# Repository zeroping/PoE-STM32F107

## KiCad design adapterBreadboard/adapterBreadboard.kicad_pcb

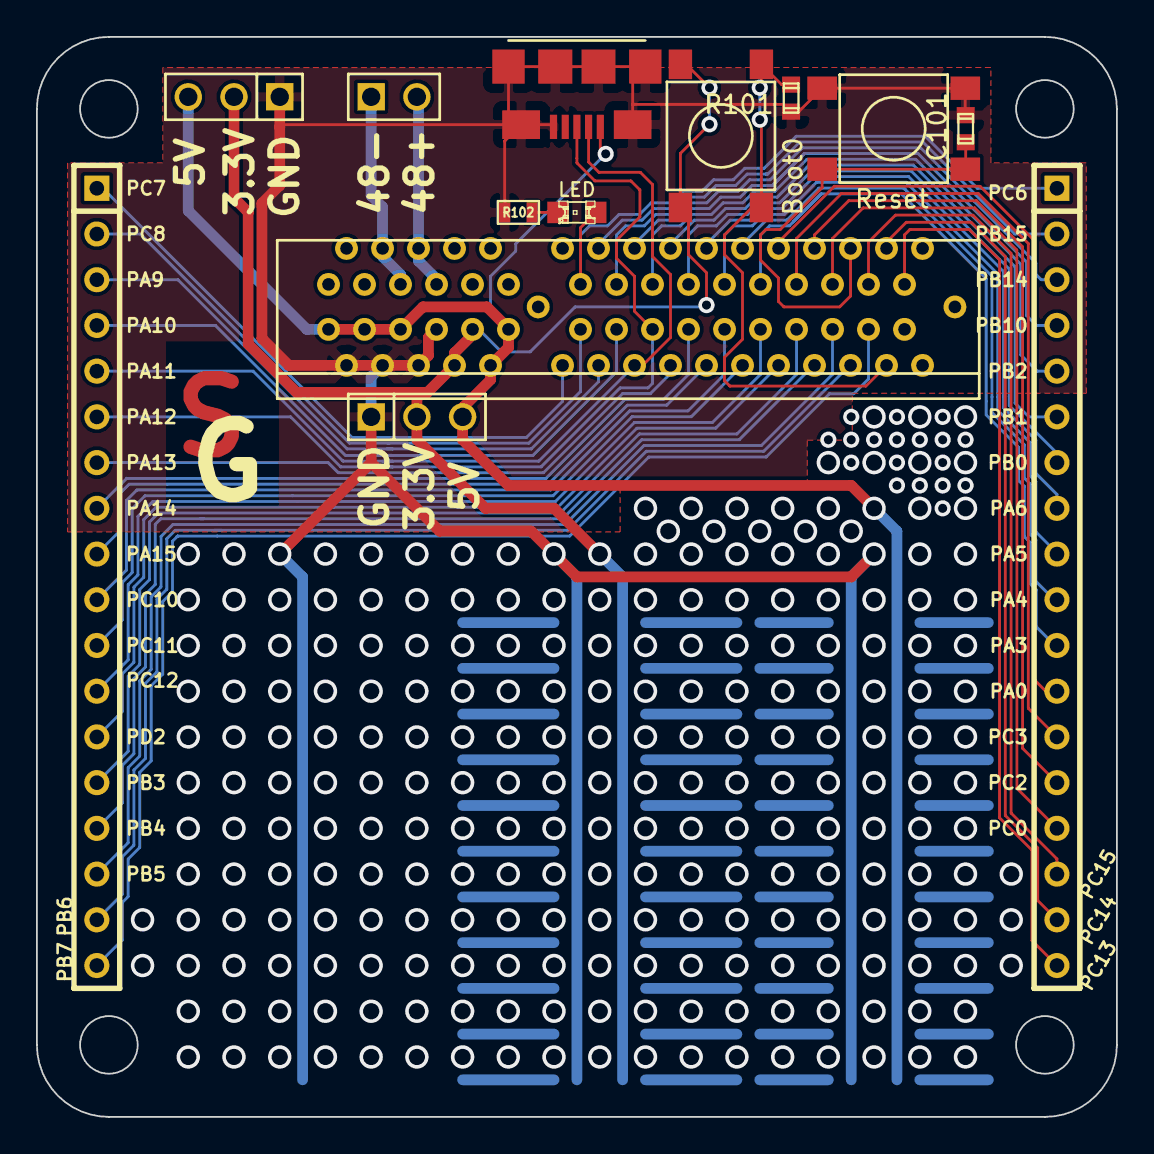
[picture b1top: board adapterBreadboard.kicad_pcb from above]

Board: 2 copper layers, 60.0 x 60.0 mm, 13 parts (0 on the bottom side), 44 nets.

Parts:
C101: 0.1uF; c_0603
D101: LED; LED-0805
J101: USB; mincro-usb
JP101: PCI-E4X_EDGE; con-pci_express(pci-e)-PCI-E_64
K101: PWR; PIN_ARRAY_3X1
K102: CONN_3; PIN_ARRAY_3X1
P101, P102: CONN_19; SIL-18
P103: CONN_2; PIN_ARRAY_2X1
R101: 10K; c_0603
R102: 220; SM0603
SW101: Boot0; tact_sw_4.3mm
SW102: Reset; tact_sw_4.3mm

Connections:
+3.3V: JP101.B8, JP101.B9, K101.2, K102.2, SW101.2
+5V: J101.1, JP101.B1, JP101.B3, JP101.B5, JP101.B10, JP101.B11, K101.3, K102.3
/+48V U +: JP101.A6, JP101.A7, P103.2
/+48V U Return: JP101.A4, JP101.A5, P103.1
/BOOT0: JP101.B30, R101.1, SW101.1
/PA0: JP101.A24, P101.12
/PA3: JP101.A23, P101.11
/PA4: JP101.A22, P101.10
/PA5: JP101.A21, P101.9
/PA6: JP101.A20, P101.8
/PA9: JP101.B14, P102.3
/PA10: JP101.B15, P102.4
/PA11: J101.2, JP101.B16, P102.5
/PA12: J101.3, JP101.B17, P102.6
/PA13: JP101.B18, P102.7
/PA14: JP101.B19, P102.8
/PA15: JP101.B20, P102.9
/PB0: JP101.A19, P101.7
/PB1: JP101.A18, P101.6
/PB2: JP101.A17, P101.5
/PB3: JP101.B25, P102.14
/PB4: JP101.B26, P102.15
/PB5: JP101.B27, P102.16
/PB6: JP101.B28, P102.17
/PB7: JP101.B29, P102.18
/PB10: JP101.A16, P101.4
/PB14: JP101.A15, P101.3
/PB15: JP101.A14, P101.2
/PC0: JP101.A27, P101.15
/PC2: JP101.A26, P101.14
/PC3: JP101.A25, P101.13
/PC6: D101.1, JP101.A13, P101.1
/PC7: JP101.B12, P102.1
/PC8: JP101.B13, P102.2
/PC10: JP101.B21, P102.10
/PC11: JP101.B22, P102.11
/PC12: JP101.B23, P102.12
/PC13: JP101.A31, P101.18
/PC14: JP101.A30, P101.17
/PC15: JP101.A29, P101.16
/PD2: JP101.B24, P102.13
/RESET: C101.1, JP101.A28, SW102.1
GND: C101.2, J101.4, J101.5, J101.6, JP101.B2, JP101.B4, JP101.B6, JP101.B7, K101.1, K102.1, R101.2, R102.2, SW102.2
unnamed: D101.2, R102.1

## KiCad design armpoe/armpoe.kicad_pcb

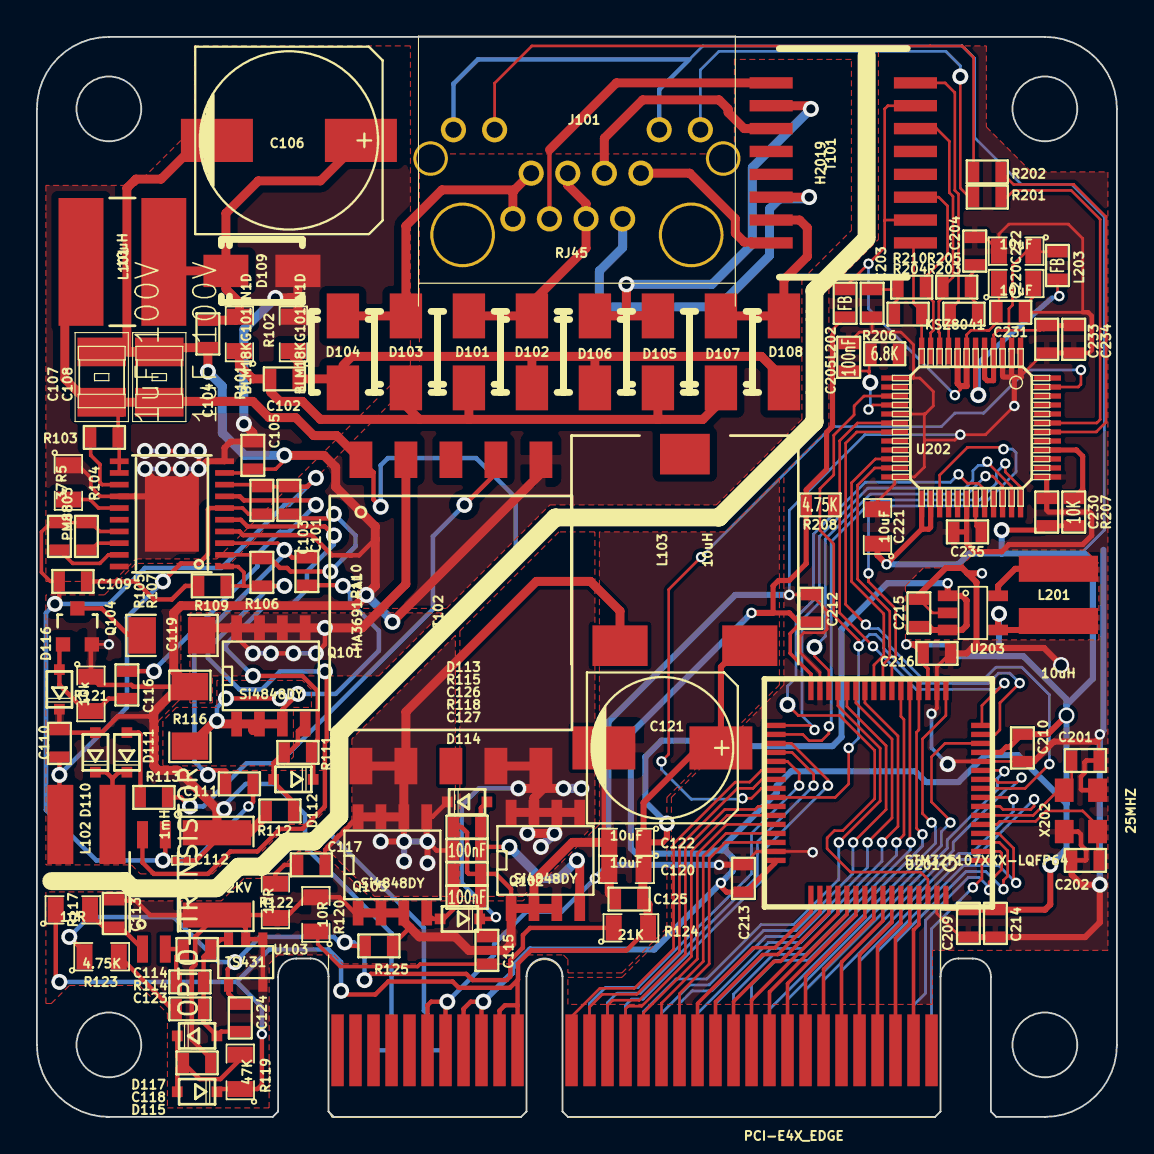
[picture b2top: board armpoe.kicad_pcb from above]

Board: 2 copper layers, 60.0 x 60.0 mm, 119 parts (0 on the bottom side), 119 nets.

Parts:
C101, C103, C110: 1uF 16V; SM0603
C102: 1nF 100V; SM0603
C104, C105: 100nF 100V; SM0603
C106: 33uF 100V; c_elec_10x10.5
C107, C108: 1uF 100V; -C1210
C109, C116, C125, C126, C127, C203, C204, C205, C210, C212, C213, C214, C230, C231, C233, C234, C235: 100nF; SM0603
C111: 470pF; SM0603
C112: 2.2nF 2KV; SM1812
C113, C118: 1uF; SM0603
C114, C123: 22nF; SM0603
C115, C117: 1nF; SM0603
C119: 47nF 200V; SM1206
C120, C122, C220, C221, C222: 10uF; SM0805
C121: 330uF; c_elec_8x10.5
C124: 100pF; SM0603
C201, C202: 18pF; SM0603
C209, C215, C216: 4.7uF; SM0603
D101, D102, D103, D104, D105, D106, D107, D108: STPS1H100A; Diode-SMA_Standard_RevA_26July2010
D109: SMAJ58A; Diode-SMA_Standard_RevA_26July2010
D110, D111, D112, D113, D114, D115, D116, D117: BAT46J; diode-SOD323-mod
J101: RJ45; RJHS-308x
JP201: PCI-E4X_EDGE; con-pci_express(pci-e)-PCI-E_4_EDGE
L101: 10uH; MSS7341
L102: 1mH; LPS4018
L103: 10uH; SER1360
L201: 10uH; LPS4018
L202, L203: FB; SM0603
Q101, Q102, Q103: Si4848DY; Si4848DY-SO8
Q104: Si2325DS; Si2325DS_SOT23
R101, R102: BLM18KG101TN1D; SM0805
R103: 24.9K; SM0603
R104: 37R5; SM0805
R105: 124k; SM0603
R106: 2.7k; SM0603
R107: 60k; SM0603
R108: 0; SM0201_r
R109: 680R; SM0603
R110, R201, R202: 510; SM0603
R111: 22R; SM0603
R112: 100k; SM0603
R113: 10; SM0603
R114: 820R; SM0603
R115, R118: 100K; SM0603
R116: 0.15; SM1206
R117, R120, R122: 10R; SM0805
R119: 47K; SM0805
R121: 10k; SM0805
R123: 4.75K; SM0805
R124: 21K; SM0805
R125, R206: 6.8K; SM0603
R203, R204, R205, R210: 50; SM0603
R207: 10K; SM0603
R208: 4.75K; SM0603
T101: H2019; T1
T102: HA3691-AL; HA3691
U101: PM8803; HTSSOP-20
U102: OPTO-TRANSISTOR; HMHA281
U103: TS431; SOT23-5
U201: STM32F107XXX-LQFP64; LQFP64
U202: KSZ8041; -TQFP48
U203: MCP1603; OS-5
X202: 25MHZ; crystal-ABM8

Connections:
+1.8V: C222.1, C233.1, C234.1, L203.1, U202.4, U202.5
+3.3V: C209.1, C210.1, C212.1, C213.1, C214.1, C216.1, C221.1, C230.1, J101.10, J101.12, JP201.B8, JP201.B9, L201.2, L202.1, R207.1, R208.1, U201.13, U201.19, U201.32, U201.48, U201.64, U202.25, U202.26, U203.4
+5V: C120.1, C121.1, C122.1, C125.1, C215.1, D115.2, JP201.B10, JP201.B11, L103.2, R117.1, R119.1, R124.2, U203.1, U203.3
/48V+ unfiltered input: C104.1, C106.1, D109.2, L101.1, R101.2
/ARTN: C101.2, C103.2, C109.1, C111.2, R105.2, R107.2, R108.2, U101.8, U101.17, U102.4
/CURRENT_SENSE: C111.1, R110.1, U101.3
/DELAY_SET: R107.1, U101.18
/FREQ_SET: R105.1, U101.19
/GAT1: D112.2, R111.1, U101.5
/GAT2: C116.1, U101.7
/MCU/A13: JP201.A13, U201.37
/MCU/A14: JP201.A14, U201.36
/MCU/A15: JP201.A15, U201.35
/MCU/A16: JP201.A16, U201.29
/MCU/A17: JP201.A17, U201.28
/MCU/A18: JP201.A18, U201.27
/MCU/A19: JP201.A19, U201.26
/MCU/A20: JP201.A20, U201.22
/MCU/A21: JP201.A21, U201.21
/MCU/A22: JP201.A22, U201.20
/MCU/A23: JP201.A23, U201.17
/MCU/A24: JP201.A24, U201.14
/MCU/A25: JP201.A25, U201.11
/MCU/A26: JP201.A26, U201.10
/MCU/A27: JP201.A27, U201.8
/MCU/A28: JP201.A28, U201.7
/MCU/A29: JP201.A29, U201.4
/MCU/A30: JP201.A30, U201.3
/MCU/A31: JP201.A31, U201.2
/MCU/A32: JP201.A32, U201.1
/MCU/B12: JP201.B12, U201.38
/MCU/B13: JP201.B13, U201.39
/MCU/B14: JP201.B14, U201.42
/MCU/B15: JP201.B15, U201.43
/MCU/B16: JP201.B16, U201.44
/MCU/B17: JP201.B17, U201.45
/MCU/B18: JP201.B18, U201.46
/MCU/B19: JP201.B19, U201.49
/MCU/B20: JP201.B20, U201.50
/MCU/B21: JP201.B21, U201.51
/MCU/B22: JP201.B22, U201.52
/MCU/B23: JP201.B23, U201.53
/MCU/B24: JP201.B24, U201.54
/MCU/B25: JP201.B25, U201.55
/MCU/B26: JP201.B26, U201.56
/MCU/B27: JP201.B27, U201.57
/MCU/B28: JP201.B28, U201.58
/MCU/B29: JP201.B29, U201.59
/MCU/B30: JP201.B30, U201.60
/MCU/B31: JP201.B31, U201.61
/MCU/ETH_INT: U201.62, U202.32
/MCU/ETH_REXT: C205.1, R206.1, U202.16
/MCU/ETH_RST: U201.40, U202.47
/MCU/LED1: J101.11, R202.2
/MCU/LED2: J101.9, R201.2
/MCU/MCO_25: U201.15, U201.41, U202.15
/MCU/RMII_CRX_DV: U201.23, U202.27
/MCU/RMII_MDC: U201.9, U202.19
/MCU/RMII_MDIO: R208.2, U201.16, U202.18
/MCU/RMII_RX0: U201.24, U202.23
/MCU/RMII_RX1: U201.25, U202.22
/MCU/RMII_TX0: U201.33, U202.35
/MCU/RMII_TX1: U201.34, U202.36
/MCU/RMII_TXEN: U201.30, U202.34
/MCU/RX+: R205.1, T101.6, U202.10
/MCU/RX-: R203.2, T101.8, U202.9
/MCU/RXCT: C220.1, C231.1, L202.2, T101.2, T101.7, U202.7, U202.8
/MCU/TX+: R204.2, T101.1, U202.12
/MCU/TX-: R210.2, T101.3, U202.11
/MCU/Unisolated 48 +: C107.1, C108.1, JP201.A6, JP201.A7, L101.2, R103.1, T102.1, U101.11, U101.12
/MCU/Unisolated 48 -: C104.2, C105.1, C106.2, C107.2, C108.2, C110.2, C112.1, D110.1, D116.2, JP201.A3, JP201.A4, Q104.S, R108.1, R112.1, R116.2, R121.1, T102.5, U101.4, U101.9
/PM8803_5V_REG: C101.1, R106.1, U101.2
/PM8803_8V_REG: C103.1, C110.1, L102.1, U101.6
/PWM_CTL: R106.2, R109.2, U101.1, U102.5
/VSS input: C105.2, D109.1, R102.2, R104.1, U101.10, U101.14, U101.PAD
/activeGate1: C126.2, D113.1, Q102.G, R115.2
/activeGate2: C127.2, D114.1, Q103.G, R118.1
/conv_out_1: C117.1, C126.1, D113.2, L103.1, Q103.D, T102.9, T102.10
/conv_out_2: C115.1, C127.1, D114.2, Q102.D, T102.6, T102.7
/primary low: C119.1, Q101.D, T102.2
GND: C112.2, C113.1, C118.1, C120.2, C121.2, C122.2, C125.2, C201.1, C202.2, C203.2, C204.1, C205.2, C209.2, C210.2, C212.2, C213.2, C214.2, C215.2, C216.2, C220.2, C221.2, C222.2, C230.2, C231.2, C233.2, C234.2, C235.2, JP201.B6, JP201.B7, Q102.S, Q103.S, R115.1, R118.2, R120.2, R122.2, R125.1, R206.2, U103.1, U103.2, U103.5, U201.12, U201.18, U201.31, U201.47, U201.63, U202.1, U202.2, U202.3, U202.13, U202.17, U202.24, U202.30, U202.37, U203.2, X202.3
unnamed: Q101.S, R110.2, R116.1
unnamed: D112.1, Q101.G, R111.2, R112.2
unnamed: C116.2, D116.1, Q104.G, R121.2
unnamed: R104.2, U101.15
unnamed: R103.2, U101.13
unnamed: R113.2, T102.4
unnamed: C117.2, R122.1
unnamed: C118.2, D115.1, D117.2, R119.2
unnamed: C114.1, R114.2, U102.2
unnamed: C109.2, R109.1
unnamed: C113.2, R117.2, U102.1
unnamed: D110.2, D111.2, L102.2
unnamed: D111.1, R113.1
unnamed: J101.2, T101.14
unnamed: D101.1, D102.2, J101.4, J101.5
unnamed: J101.6, T101.9
unnamed: D103.1, D104.2, J101.7, J101.8
unnamed: C102.1, D101.2, D103.2, D105.2, D107.2, R101.1
unnamed: C102.2, D102.1, D104.1, D106.1, D108.1, R102.1
unnamed: J101.3, T101.11
unnamed: D107.1, D108.2, T101.15
unnamed: J101.1, T101.16
unnamed: C114.2, C123.1, C124.1, D117.1, R114.1, U103.3
unnamed: C123.2, R123.2
unnamed: C124.2, R123.1, R124.1, R125.2, U103.4
unnamed: D105.1, D106.2, T101.10
unnamed: C119.2, Q104.D
unnamed: C115.2, R120.1
unnamed: R202.1, U202.42
unnamed: C203.1, R204.1, R210.1
unnamed: R201.1, U202.43
unnamed: R207.2, U202.40
unnamed: C235.1, U202.31
unnamed: C202.1, U201.5, X202.1
unnamed: C201.2, U201.6, X202.2
unnamed: L203.2, U202.6
unnamed: L201.1, U203.5
unnamed: C204.2, R203.1, R205.2

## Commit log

2013-09-29 initial checkin
2013-10-01 looks to be a complete board, pending a check with the BOM and a good look-over
2013-10-04 swapped passives to match what I can order.
2013-10-09 All routed. Again.
2014-01-30 This is what was sent off, I belive. I'm in the process fo fixing the errors now
2014-01-30 fixed pci express card slot size
2014-02-12 most of the fixes form V1. looking to change pinout.
2014-02-12 got everything rerouted, still haven't changed pinout. Still need to route int line.
2014-05-15 looks done, except the connector needs to be moved over (which will suck)
2014-05-15 Moved connector. Mostly finished.
2014-05-16 As ordered the first time, but with a fix for the resistor
2014-07-11 Not sure what changed -old commit
